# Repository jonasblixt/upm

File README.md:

## UPM - USB Power Monitor

This device monitors current and voltage for USB powered devices.

# Hardware

Assembled PCB 

The PCB is a four layer board, manufactured by OSH Park. The boards can
 be ordered [here](https://oshpark.com/shared_projects/uE5lZDkP)

Schematics, layout and BOM can be found [here](https://github.com/jonpe960/upm/tree/master/hw/Release/R1)

# System description

The device has a built in, two port, USB hub. One of the down stream ports
connects to the USB A connector and the other down stream port is connected to
the microcontroller.

An integrade analog frontend that contains a 16 bit ADC and differential
amplifier measures the voltage and current of the down stream VBUS supply. Three
auxillary diff inputs are available on a pin header.

It is possible to control the output VBUS with the on board power switch, which
also has built in short circuit protection. Three auxillary, open collector,
outputs are available on pin header.

# Ncurses TUI

The ncurses based TUI, displaying voltage, current and energy usage. 
Outputs can be controled from the TUI:
 - A/a VBUS on/off
 - S/s out1 on/off
 - D/d out2 on/off
 - F/f out3 on/off
 - r Reset energy counters

# Intended usage

This project came from a need to remotley monitor and power cycle USB powered devices.

# Future improvements

 - Add domain/tcp socket listener for remote control
 - Support for logging

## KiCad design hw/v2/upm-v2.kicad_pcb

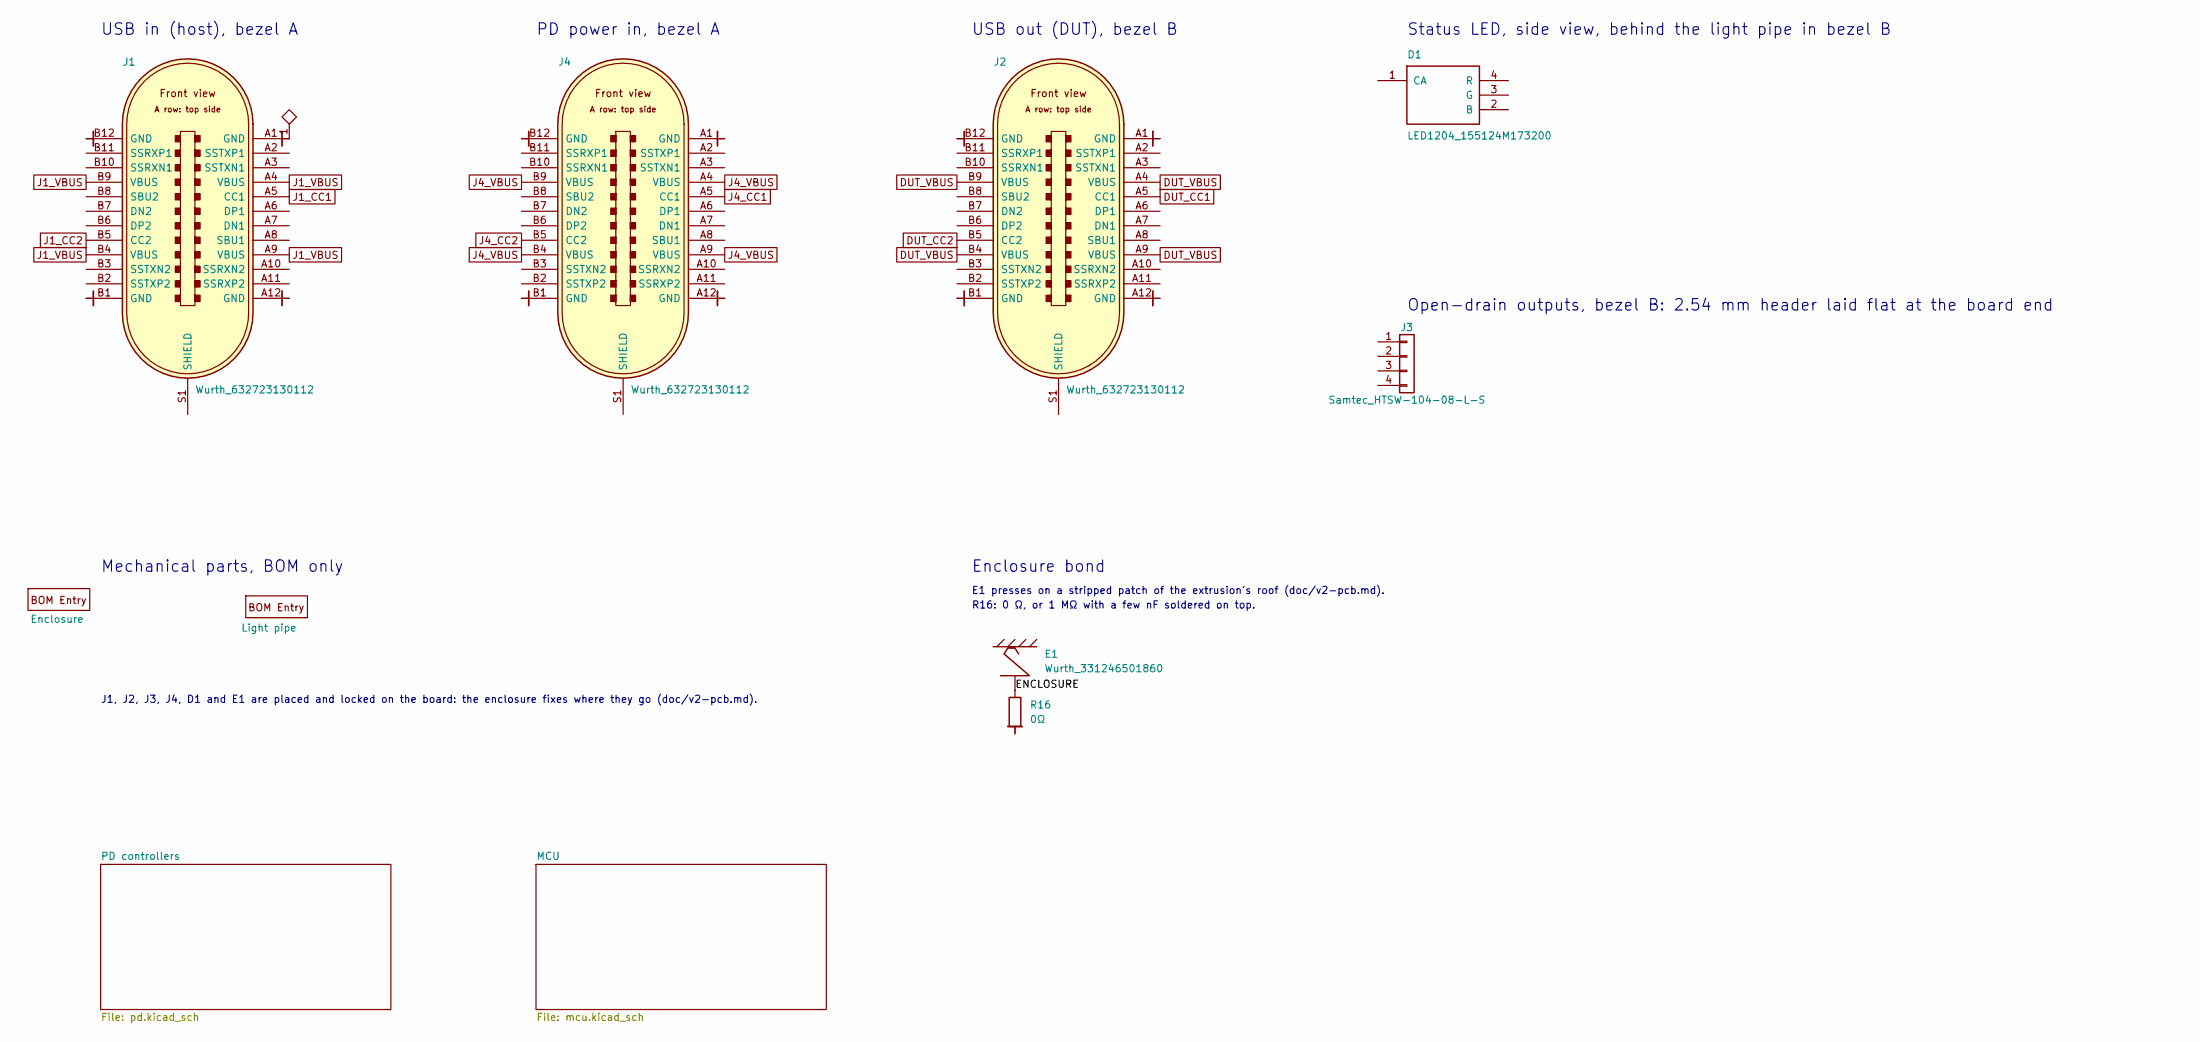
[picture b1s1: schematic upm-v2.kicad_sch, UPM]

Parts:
D1: LED1204_155124M173200; LED_Wurth_155124M173200_3.2x1.5mm_Horizontal; Part Number 155124M173200
E1: Wurth_331246501860; Part Number 331246501860
J1, J2, J4: Wurth_632723130112; Part Number 632723130112
J3: Samtec_HTSW-104-08-L-S; Samtec_HTSW-104-08-L-S_EdgeMount; Part Number HTSW-104-08-L-S
M1: Enclosure; Part Number 1455A802
M2: Light pipe; Part Number 515-1351-0188F
R16: 0Ω; R_0603_1608Metric; Part Number CRCW06030000Z0EA

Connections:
/ENCLOSURE: E1.1, R16.1
DUT_CC1: J2.A5 (CC1); also elsewhere on the board
DUT_CC2: J2.B5 (CC2); also elsewhere on the board
DUT_VBUS: J2.A4 (VBUS), J2.A9 (VBUS), J2.B4 (VBUS), J2.B9 (VBUS); also elsewhere on the board
GND: J1.A1 (GND), J1.A12 (GND), J1.B1 (GND), J1.B12 (GND), J2.A1 (GND), J2.A12 (GND), J2.B1 (GND), J2.B12 (GND), J4.A1 (GND), J4.A12 (GND), J4.B1 (GND), J4.B12 (GND), R16.2; also elsewhere on the board
J1_CC1: J1.A5 (CC1); also elsewhere on the board
J1_CC2: J1.B5 (CC2); also elsewhere on the board
J1_VBUS: J1.A4 (VBUS), J1.A9 (VBUS), J1.B4 (VBUS), J1.B9 (VBUS)
J4_CC1: J4.A5 (CC1); also elsewhere on the board
J4_CC2: J4.B5 (CC2); also elsewhere on the board
J4_VBUS: J4.A4 (VBUS), J4.A9 (VBUS), J4.B4 (VBUS), J4.B9 (VBUS); also elsewhere on the board

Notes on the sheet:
USB out (DUT), bezel B
J1, J2, J3, J4, D1 and E1 are placed and locked on the board: the enclosure fixes where they go (doc/v2-pcb.md).
USB in (host), bezel A
Mechanical parts, BOM only
Open-drain outputs, bezel B: 2.54 mm header laid flat at the board end
Status LED, side view, behind the light pipe in bezel B
PD power in, bezel A
Enclosure bond
E1 presses on a stripped patch of the extrusion's roof (doc/v2-pcb.md).
R16: 0 Ω, or 1 MΩ with a few nF soldered on top.

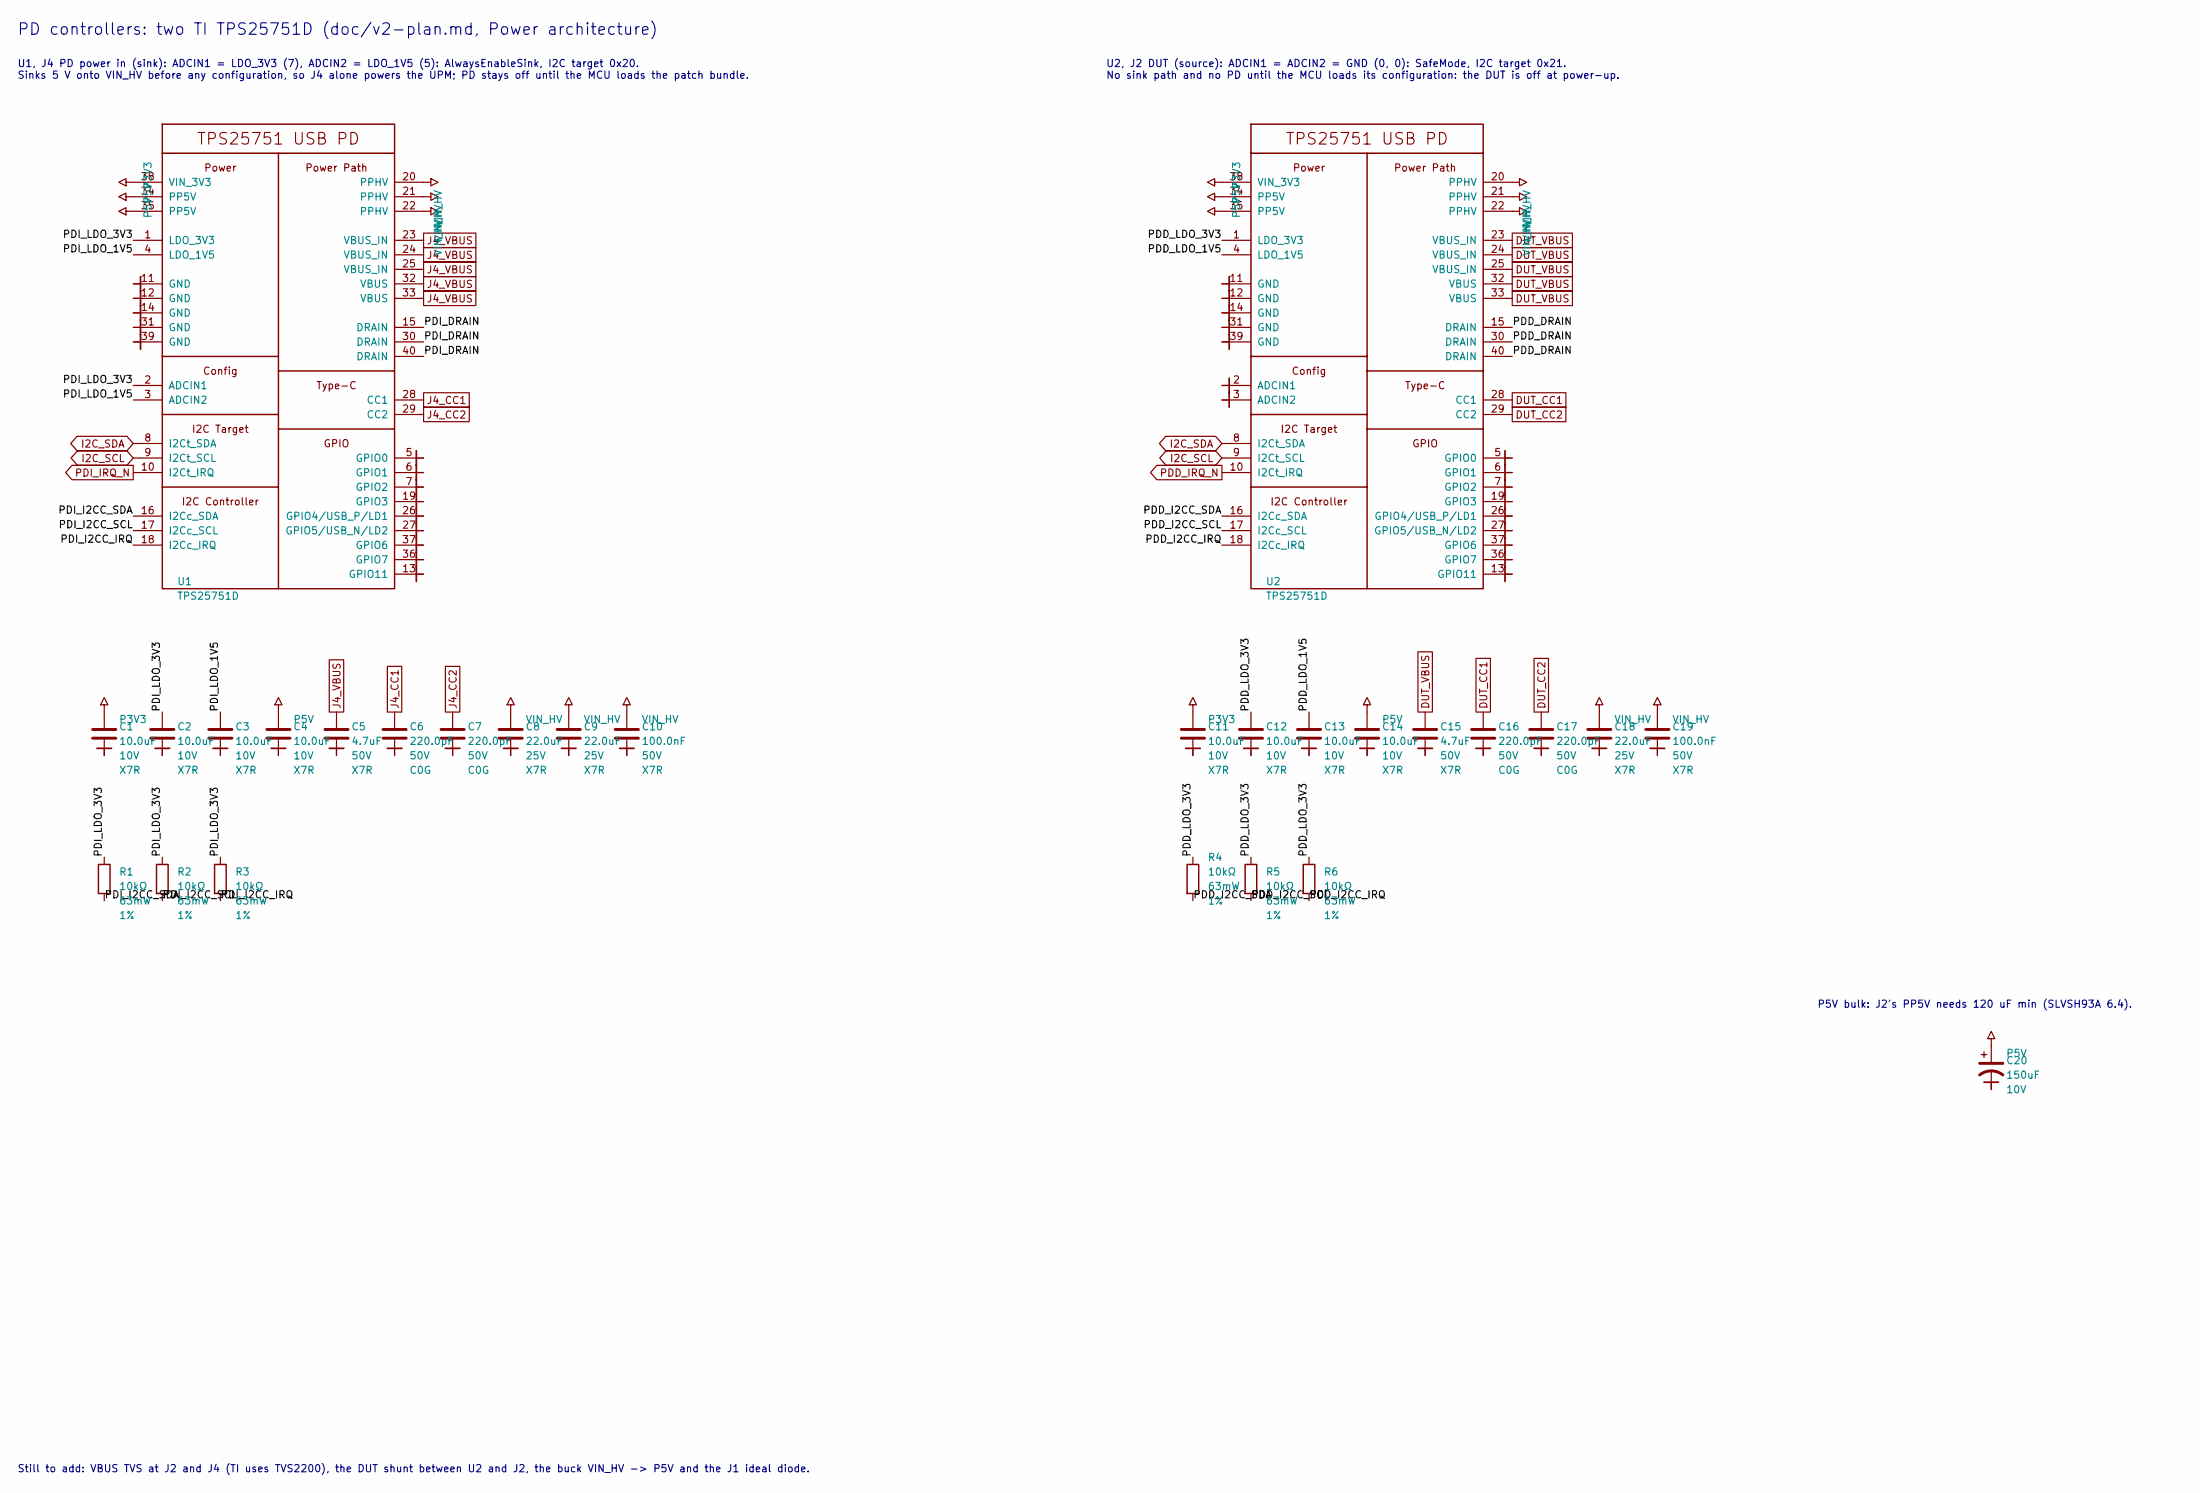
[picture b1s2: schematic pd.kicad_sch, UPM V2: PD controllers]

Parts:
C1, C2, C3, C4, C11, C12, C13, C14: 10.0uF; C_0603_1608Metric; Voltage 10V; Part Number GRM188Z71A106KA73
C5, C15: 4.7uF; C_1206_3216Metric; Voltage 50V; Part Number GRM31CR71H475KA12
C6, C7, C16, C17: 220.0pF; C_0402_1005Metric; Voltage 50V; Part Number GRM1555C1H221JA01
C8, C9, C18: 22.0uF; C_1210_3225Metric; Voltage 25V; Part Number GRM32ER71E226KE15
C10, C19: 100.0nF; C_0402_1005Metric; Voltage 50V; Part Number GRM155R71H104KE14
C20: 150uF; CP_EIA-7343-30_AVX-N; Voltage 10V; Part Number 10TPE150MPL
R1, R2, R3, R4, R5, R6: 10kΩ; R_0402_1005Metric; Tolerance 1%; Part Number CRCW040210K0FKED
U1, U2: TPS25751D; Texas_REF0038A_WQFN-38-2EP_4x6mm_P0.4mm; Part Number TPS25751DREFR

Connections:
/PD controllers/PDD_DRAIN: U2.15 (DRAIN), U2.30 (DRAIN), U2.40 (DRAIN)
/PD controllers/PDD_I2CC_IRQ: R6.2, U2.18 (I2Cc_IRQ)
/PD controllers/PDD_I2CC_SCL: R5.2, U2.17 (I2Cc_SCL)
/PD controllers/PDD_I2CC_SDA: R4.2, U2.16 (I2Cc_SDA)
/PD controllers/PDD_LDO_1V5: C13.1, U2.4 (LDO_1V5)
/PD controllers/PDD_LDO_3V3: C12.1, R4.1, R5.1, R6.1, U2.1 (LDO_3V3)
/PD controllers/PDI_DRAIN: U1.15 (DRAIN), U1.30 (DRAIN), U1.40 (DRAIN)
/PD controllers/PDI_I2CC_IRQ: R3.2, U1.18 (I2Cc_IRQ)
/PD controllers/PDI_I2CC_SCL: R2.2, U1.17 (I2Cc_SCL)
/PD controllers/PDI_I2CC_SDA: R1.2, U1.16 (I2Cc_SDA)
/PD controllers/PDI_LDO_1V5: C3.1, U1.3 (ADCIN2), U1.4 (LDO_1V5)
/PD controllers/PDI_LDO_3V3: C2.1, R1.1, R2.1, R3.1, U1.1 (LDO_3V3), U1.2 (ADCIN1)
DUT_CC1: C16.1, U2.28 (CC1); also elsewhere on the board
DUT_CC2: C17.1, U2.29 (CC2); also elsewhere on the board
DUT_VBUS: C15.1, U2.23 (VBUS_IN), U2.24 (VBUS_IN), U2.25 (VBUS_IN), U2.32 (VBUS), U2.33 (VBUS); also elsewhere on the board
GND: C1.2, C2.2, C3.2, C4.2, C5.2, C6.2, C7.2, C8.2, C9.2, C10.2, C11.2, C12.2, C13.2, C14.2, C15.2, C16.2, C17.2, C18.2, C19.2, C20.2, U1.5 (GPIO0), U1.6 (GPIO1), U1.7 (GPIO2), U1.11 (GND), U1.12 (GND), U1.13 (GPIO11), U1.14 (GND), U1.19 (GPIO3), U1.26 (GPIO4/USB_P/LD1), U1.27 (GPIO5/USB_N/LD2), U1.31 (GND), U1.36 (GPIO7), U1.37 (GPIO6), U1.39 (GND), U2.2 (ADCIN1), U2.3 (ADCIN2), U2.5 (GPIO0), U2.6 (GPIO1), U2.7 (GPIO2), U2.11 (GND), U2.12 (GND), U2.13 (GPIO11), U2.14 (GND), U2.19 (GPIO3), U2.26 (GPIO4/USB_P/LD1), U2.27 (GPIO5/USB_N/LD2), U2.31 (GND), U2.36 (GPIO7), U2.37 (GPIO6), U2.39 (GND); also elsewhere on the board
I2C_SCL: U1.9 (I2Ct_SCL), U2.9 (I2Ct_SCL); also elsewhere on the board
I2C_SDA: U1.8 (I2Ct_SDA), U2.8 (I2Ct_SDA); also elsewhere on the board
J4_CC1: C6.1, U1.28 (CC1); also elsewhere on the board
J4_CC2: C7.1, U1.29 (CC2); also elsewhere on the board
J4_VBUS: C5.1, U1.23 (VBUS_IN), U1.24 (VBUS_IN), U1.25 (VBUS_IN), U1.32 (VBUS), U1.33 (VBUS); also elsewhere on the board
P3V3: C1.1, C11.1, U1.38 (VIN_3V3), U2.38 (VIN_3V3); also elsewhere on the board
P5V: C4.1, C14.1, C20.1, U1.34 (PP5V), U1.35 (PP5V), U2.34 (PP5V), U2.35 (PP5V)
PDD_IRQ_N: U2.10 (I2Ct_IRQ); also elsewhere on the board
PDI_IRQ_N: U1.10 (I2Ct_IRQ); also elsewhere on the board
VIN_HV: C8.1, C9.1, C10.1, C18.1, C19.1, U1.20 (PPHV), U1.21 (PPHV), U1.22 (PPHV), U2.20 (PPHV), U2.21 (PPHV), U2.22 (PPHV)

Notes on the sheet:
Still to add: VBUS TVS at J2 and J4 (TI uses TVS2200), the DUT shunt between U2 and J2, the buck VIN_HV -> P5V and the J1 ideal diode.
P5V bulk: J2's PP5V needs 120 uF min (SLVSH93A 6.4).
U1, J4 PD power in (sink): ADCIN1 = LDO_3V3 (7), ADCIN2 = LDO_1V5 (5): AlwaysEnableSink, I2C target 0x20. Sinks 5 V onto VIN_HV before any configuration, so J4 alone powers the UPM; PD stays off until the MCU loads the patch bundle.
U2, J2 DUT (source): ADCIN1 = ADCIN2 = GND (0, 0): SafeMode, I2C target 0x21. No sink path and no PD until the MCU loads its configuration: the DUT is off at power-up.
PD controllers: two TI TPS25751D (doc/v2-plan.md, Power architecture)

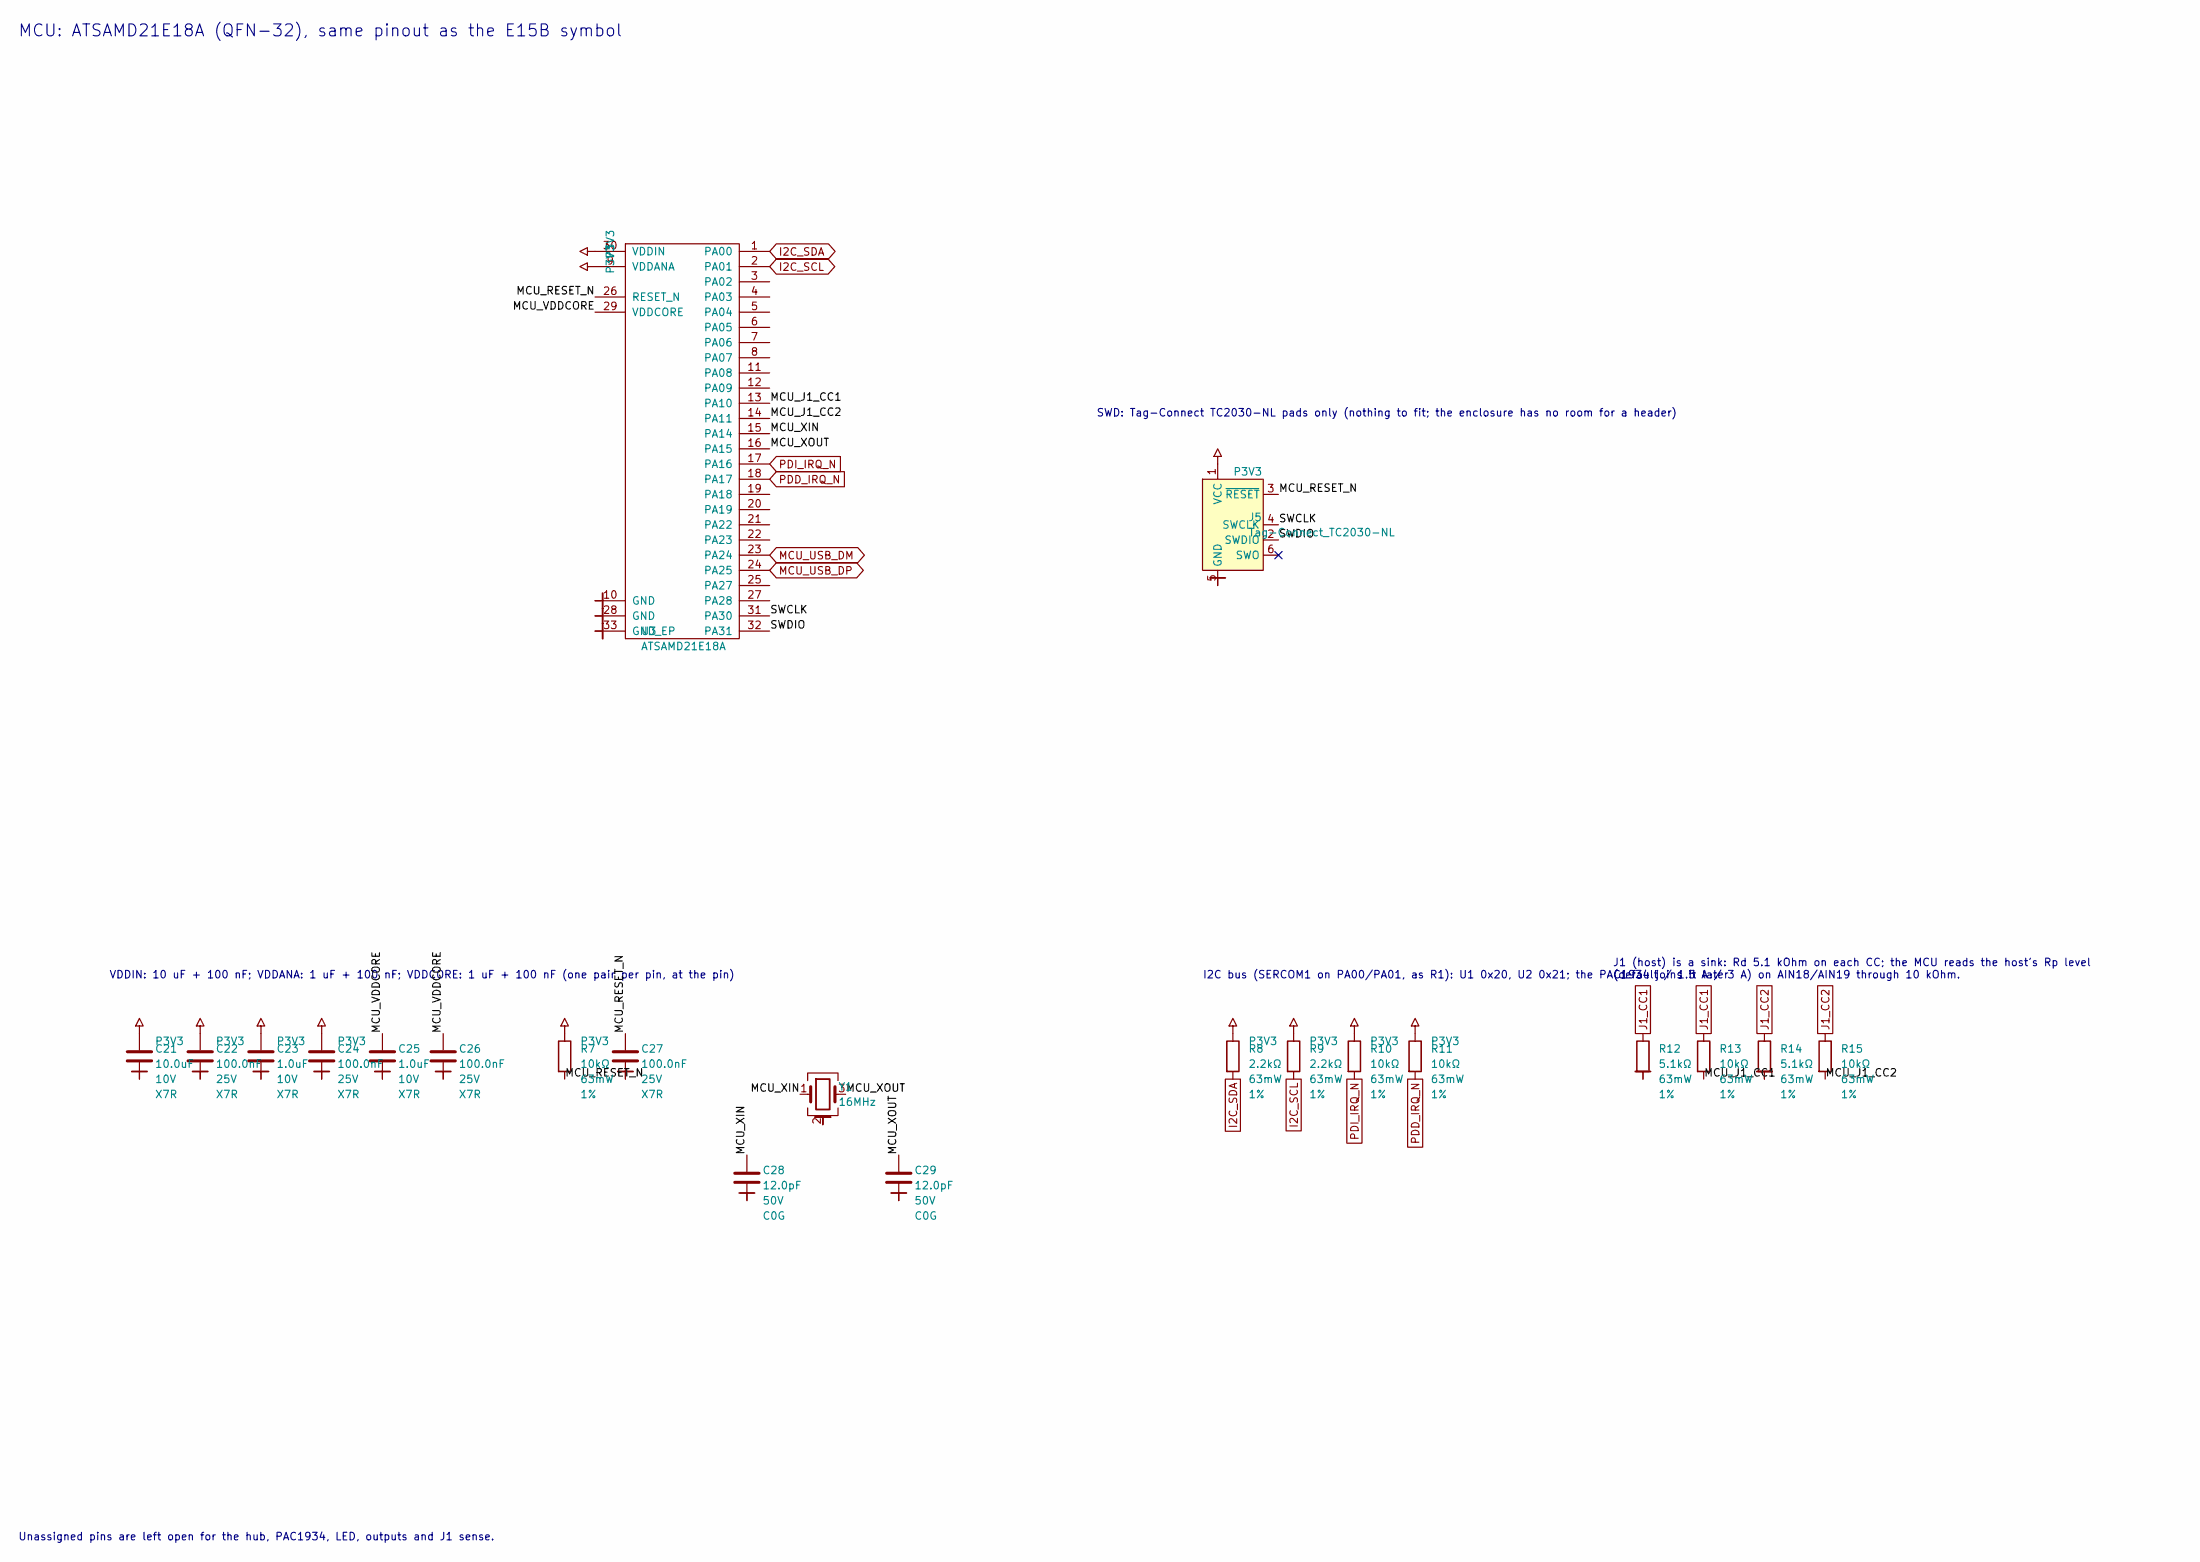
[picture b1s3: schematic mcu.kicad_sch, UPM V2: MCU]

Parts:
C21: 10.0uF; C_0603_1608Metric; Voltage 10V; Part Number GRM188Z71A106KA73
C22, C24, C26, C27: 100.0nF; C_0402_1005Metric; Voltage 25V; Part Number GRM155R71E104KE14
C23, C25: 1.0uF; C_0402_1005Metric; Voltage 10V; Part Number GRM155Z71A105KE01
C28, C29: 12.0pF; C_0402_1005Metric; Voltage 50V; Part Number GRM1555C1H120JA01
J5: Tag-Connect_TC2030-NL; Tag-Connect_TC2030-IDC-NL_2x03_P1.27mm_Vertical
R7, R10, R11, R13, R15: 10kΩ; R_0402_1005Metric; Tolerance 1%; Part Number CRCW040210K0FKED
R8, R9: 2.2kΩ; R_0402_1005Metric; Tolerance 1%; Part Number CRCW04022K20FKED
R12, R14: 5.1kΩ; R_0402_1005Metric; Tolerance 1%; Part Number CRCW04025K10FKED
U3: ATSAMD21E18A; QFN-32-1EP_5x5mm_P0.5mm_EP3.6x3.6mm; Part Number ATSAMD21E18A-MUT
Y1: 16MHz; Crystal_SMD_NDK_NX2520SA-4Pin_2.5x2.0mm; Frequency Tolerance ±10ppm; Part Number NX2520SA-16.000000MHZ

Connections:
/MCU/MCU_J1_CC1: R13.2, U3.13 (PA10)
/MCU/MCU_J1_CC2: R15.2, U3.14 (PA11)
/MCU/MCU_RESET_N: C27.1, J5.3 (~RESET), R7.2, U3.26 (RESET_N)
/MCU/MCU_VDDCORE: C25.1, C26.1, U3.29 (VDDCORE)
/MCU/MCU_XIN: C28.1, U3.15 (PA14), Y1.1
/MCU/MCU_XOUT: C29.1, U3.16 (PA15), Y1.3
/MCU/SWCLK: J5.4 (SWCLK), U3.31 (PA30)
/MCU/SWDIO: J5.2 (SWDIO), U3.32 (PA31)
GND: C21.2, C22.2, C23.2, C24.2, C25.2, C26.2, C27.2, C28.2, C29.2, J5.5 (GND), R12.2, R14.2, U3.10 (GND), U3.28 (GND), U3.33 (GND_EP), Y1.2 (G), Y1.4 (G); also elsewhere on the board
I2C_SCL: R9.2, U3.2 (PA01); also elsewhere on the board
I2C_SDA: R8.2, U3.1 (PA00); also elsewhere on the board
J1_CC1: R12.1, R13.1; also elsewhere on the board
J1_CC2: R14.1, R15.1; also elsewhere on the board
MCU_USB_DM: U3.23 (PA24)
MCU_USB_DP: U3.24 (PA25)
P3V3: C21.1, C22.1, C23.1, C24.1, J5.1 (VCC), R7.1, R8.1, R9.1, R10.1, R11.1, U3.9 (VDDANA), U3.30 (VDDIN); also elsewhere on the board
PDD_IRQ_N: R11.2, U3.18 (PA17); also elsewhere on the board
PDI_IRQ_N: R10.2, U3.17 (PA16); also elsewhere on the board

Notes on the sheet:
I2C bus (SERCOM1 on PA00/PA01, as R1): U1 0x20, U2 0x21; the PAC1934 joins it later
SWD: Tag-Connect TC2030-NL pads only (nothing to fit; the enclosure has no room for a header)
VDDIN: 10 uF + 100 nF; VDDANA: 1 uF + 100 nF; VDDCORE: 1 uF + 100 nF (one pair per pin, at the pin)
J1 (host) is a sink: Rd 5.1 kOhm on each CC; the MCU reads the host's Rp level (default / 1.5 A / 3 A) on AIN18/AIN19 through 10 kOhm.
Unassigned pins are left open for the hub, PAC1934, LED, outputs and J1 sense.
MCU: ATSAMD21E18A (QFN-32), same pinout as the E15B symbol

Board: 4 copper layers, 56 parts (0 on the bottom side), 38 nets, no tracks yet.

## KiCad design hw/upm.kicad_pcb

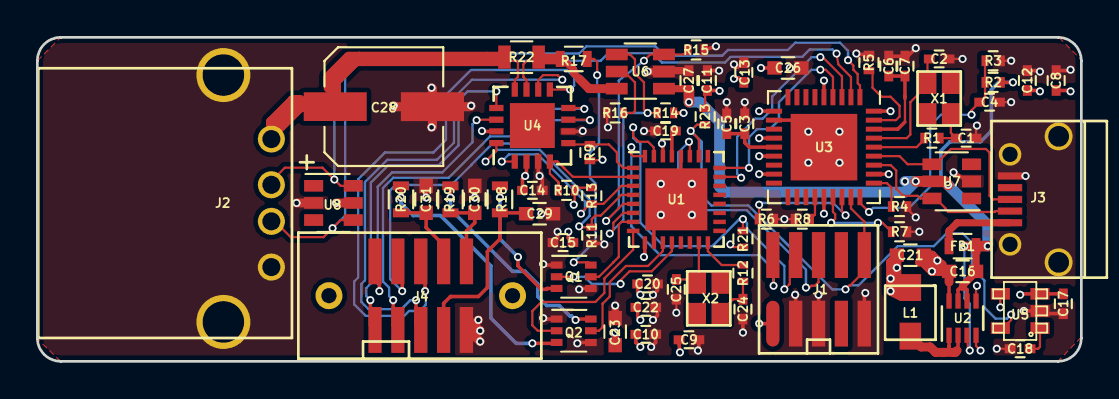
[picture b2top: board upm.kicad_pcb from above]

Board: 4 copper layers, 58.0 x 18.0 mm, 72 parts (0 on the bottom side), 57 nets.

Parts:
C1, C2, C24, C25: C0402_12p_25Vdc_C0G_2; C0402
C3, C6, C18: C0402_100n_25Vdc_X7R; C0402
C4, C5, C7, C8, C9, C10, C11, C12, C13, C14, C15, C17, C19, C20, C22, C27: C0402_1u_6.3Vdc_X7R; C0402
C16, C21, C23, C26: C0603_10u_10Vdc_X7R; C0603
C28: PCAP_120u_4; CP_Elec_6.3x5.8
C29, C30, C31: C0603_22n_100Vdc_X7R; C0603
FB1: BL0603_BLM18BB121SN1D; L0603
J1: FTSH-105-01-F-DV-K
J2: USB_A_292303-1; USB_A_TH
J3: DX4R005JJ2R1800; USB_Micro-B
J4: TFM-105-02-S-D-WT
L1: IHLP1212_1u_1; IHLP1212
Q1, Q2: PUMH13; SOT-363_SC-70-6
R1, R12: R0402_100R; R0402
R2, R3, R4, R6, R7, R8, R11, R13, R14, R15, R23: R0402_46k40; R0402
R5: R0402_12k10; R0402
R9, R10: R0402_2k20; R0402
R16: R0402_21k; R0402
R17: R0603_200R; R0603
R18, R19, R20: R0603_51R; R0603
R21: R0402_1k; R0402
R22: R0805_0R1; R0805
U1: ATSAMD21E15B; QFN-32-1EP_5x5mm_Pitch0.5mm
U2: MIC23150-SYMT; DFN-8_2x2mm_Pitch0.5mm
U3: USB2512B; QFN-36-1EP_6x6mm_Pitch0.5mm
U4: PAC1934; QFN-16-1EP_4x4mm_Pitch0.65mm
U5: LP3470IM5X-3.08_NOPB; SOT-23-5
U6: NCP380HSNAJAAT1G; TSOT-23-6
U7, U8: USBLC6-4; SOT-23-6
X1: NX2520SA-24.000000MHZ; NX2520SA
X2: NX2520SA-16.000000MHZ; NX2520SA

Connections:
/DUT_DISCHARGE: Q1.2, U1.12
/DUT_USB_D_N: J2.2, U3.1, U8.6
/DUT_USB_D_P: J2.3, U3.2, U8.4
/DUT_USB_EN: R15.2, U1.5, U6.3
/DUT_USB_FLAG_N: R14.1, U1.6, U6.4
/DUT_USB_VBUS: C28.1, J2.1, R22.1, U4.12, U8.5
/I2C_SCL: R10.2, U1.2, U4.4
/I2C_SDA: R9.2, U1.1, U4.5
/OUT1_EN: Q1.5, U1.7
/OUT2_EN: Q2.2, U1.8
/OUT3_EN: Q2.5, U1.11
/PAC_ALERT_N: R13.1, U1.3, U4.1
/PAC_PWRDN_N: R11.2, U1.4, U4.16
/RST_N: J1.10, R23.1, U1.26, U3.26, U5.5
/SNS2_N: J4.9, U4.14
/SNS2_P: J4.10, U4.13
/SNS3_N: J4.7, U4.7
/SNS3_P: J4.8, U4.8
/SNS4_N: J4.5, U4.9
/SNS4_P: J4.6, U4.10
/SWCLK: J1.4, R21.2, U1.31
/SWDIO: J1.2, U1.32
/SWO: J1.6, U1.27
/UC_USB_D_N: U1.23, U3.3
/UC_USB_D_P: U1.24, U3.4
/USB_D_N: J3.2, U3.30, U7.6
/USB_D_P: J3.3, U3.31, U7.4
/VDDCORE: C19.1, U1.29
/XTAL_IN: C25.1, U1.15, X2.3
/XTAL_OUT: R12.2, U1.16
GND: C1.2, C2.2, C3.2, C4.2, C5.2, C6.2, C7.2, C8.2, C9.2, C10.2, C11.2, C12.2, C13.2, C14.2, C15.2, C16.2, C17.2, C18.2, C19.2, C20.2, C21.2, C22.2, C23.2, C24.2, C25.2, C26.2, C27.2, C28.2, C29.2, C30.2, C31.2, J1.3, J1.5, J1.9, J2.4, J2.5, J2.6, J3.5, J3.6, J3.7, J4.2, Q1.1, Q1.4, Q2.1, Q2.4, R3.1, R4.2, R5.2, R6.1, R7.1, R8.1, R11.1, R15.1, R16.2, U1.10, U1.28, U1.33, U2.5, U2.8, U3.11, U3.37, U4.3, U4.6, U5.2, U6.2, U7.2, U8.2
unnamed: C1.1, R1.2, X1.1
unnamed: C2.1, U3.33, X1.3
unnamed: C3.1, C5.1, U3.14
unnamed: C4.1, R2.1, R3.2, U3.27
unnamed: C6.1, C7.1, U3.34
unnamed: C18.1, U5.1
unnamed: C24.1, R12.1, X2.1
unnamed: C29.1, J4.4, R18.1
unnamed: C30.1, J4.1, R19.1
unnamed: C31.1, J4.3, R20.1
unnamed: FB1.1, J3.1
unnamed: L1.1, U2.1, U2.2
unnamed: Q1.3, R18.2
unnamed: Q1.6, R17.2
unnamed: Q2.3, R20.2
unnamed: Q2.6, R19.2
unnamed: R1.1, U3.32
unnamed: R4.1, U3.28
unnamed: R5.1, U3.35
unnamed: R6.2, U3.25
unnamed: R7.2, U3.24
unnamed: R8.2, U3.22
unnamed: R16.1, U6.5
unnamed: R17.1, R22.2, U4.11, U6.6
P3V3: C8.1, C9.1, C10.1, C11.1, C12.1, C13.1, C14.1, C15.1, C17.1, C20.1, C21.1, C22.1, C23.1, C26.1, J1.1, L1.2, R9.1, R10.1, R13.2, R14.2, R21.1, R23.2, U1.9, U1.30, U2.4, U3.5, U3.10, U3.13, U3.15, U3.17, U3.23, U3.29, U3.36, U4.2, U4.15, U5.3, U5.4
P5V0: C16.1, C27.1, FB1.2, R2.2, U2.3, U2.6, U2.7, U6.1, U7.5

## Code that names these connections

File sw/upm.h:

/**
 * UPM
 *
 * Copyright (C) 2018 Jonas Persson <jonpe960@gmail.com>
 *
 * SPDX-License-Identifier: BSD-3-Clause
 *
 */

#ifndef __UPM_H__
#define __UPM_H__

#define PIN_SDA            PIN_PA0
#define PIN_SCL            PIN_PA1
#define PIN_PAC_ALERT_N    PIN_PA2
#define PIN_PACPWRDN_N     PIN_PA3
#define PIN_DUT_USB_EN     PIN_PA4
#define PIN_DUT_USB_FLAG_N PIN_PA5
#define PIN_OUT1_EN        PIN_PA6
#define PIN_OUT2_EN        PIN_PA7
#define PIN_OUT3_EN        PIN_PA8
#define PIN_DUT_DISCHARGE  PIN_PA9
#define PIN_XTAL_IN        PIN_PA14
#define PIN_XTAL_OUT       PIN_PA15
#define PIN_USB_DM         PIN_PA24
#define PIN_USB_DP         PIN_PA25
#define PIN_SWO            PIN_PA28
#define PIN_SWCLK          PIN_PA30
#define PIN_SWDIO          PIN_PA31

#define UNUSED_PINS (   PIN_PA10 | \
                        PIN_PA11 | \
                        PIN_PA16 | \
                        PIN_PA17 | \
                        PIN_PA18 | \
                        PIN_PA19 | \
                        PIN_PA22 | \
                        PIN_PA23 | \
                        PIN_PA27)

#endif

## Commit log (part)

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2018-09-04 Initial structure
2018-09-04 Added some datasheets
2018-09-13 R1 release of HW
2018-09-13 Removed DS_store -files
2018-09-14 Added BOM
2018-09-15 Updated gitignore
2018-12-09 First working version
2018-12-09 Updated documentation
2018-12-09 Added licensing info
2019-01-15 Added timeout, under some circumstances the USB link can break down. Unless there is a timeout the device will be stuck for ever.
